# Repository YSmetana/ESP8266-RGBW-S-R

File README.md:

View this project on [CADLAB.io](https://cadlab.io/project/24310). 

# ESP8266-RGBW-S-R

**ESP8266**-based **RGBW** controller with **S**ensor and **R**elay support.

This harware design (PCB) is based on the [ESP-GO project and Hackitt & Bodgitt board](https://tech.scargill.net/home-control-2018/) created by [Pete Scargill](https://tech.scargill.net/) and [Aidan Ruff](https://www.scargill.net/cv/).

## PCB
96x55 mm.
### Render

### Actual photos
## Power supply
AC 110-220V or DC 5V, DC 5-24V.

### AC 110-220V, 5V needed
Use **PSU-A** HLK-PM01, output DC 5V. DC 3.3V via onboard LM1117-3.3.

### AC 110-220V, NO 5V needed
Use **PSU-D** HLK-2M03, output DC 3.3V. Short J4 to supply 3.3V directly from DC-DC convertor.

### DC 5V
Use **PSU-B** B0503S, output DC 3.3V. No onboard 3.3 regulator needed. Short J4 to supply 3.3V directly from DC-DC convertor.

### DC 5-24V
Use **PSU-C** LM2596-based buck convertor. Set output to 5V and use onboard LM1117-3.3. Or set output to 3.3V and short **J4** to supply 3.3V directly from DC-DC convertor.

## Errors found

In version **0.7** I was trying to use pull-down resistors for PWM output pins, but it turned out that ESP can not start if TX (GPIO1) pin is pulled low during the boot. So please just **remove R25** (don't solder it). PWM works fine without it (and probably without R22-R24 too :) ), and it was not in the original version.

I did not use R8 (remove) either because it seems it is duplicated by R11.

Apparently, GPIO4 and GPIO5 are misplaced on the schematic (correct on the PCB footprint).

## Soldering

### Basic

#### SMD
* LK2 - just short it if you use LED strip and use input power for them.
* R3
* R4
* R5
* R7
* R10
* R11
* R16
* R12
* C5
* C6
* ESP (sometimes better to solder manually to avoid shotage under the ESP)

If using non 3.3V input and need on-board linear converter:
* C2
* C3
* C4
* C22
* C27
* IC6

Short JP4 **only if you have 3.3V input** already and do not need any extra converters. Input 5V line will be directly connected with internal 3.3V line.

#### THT
* C1 (not nessecery with a good DC-DC converter with capacitor on-board)
* LED2 (status)
* X1 (for PWM RGBW) 
* JP10 (for programming)
* PSU (check voltage on regulated converters). See «Power supply» section above.

## Temp/Humidity sensor, IC2
### SMD
* R21

## PWM RGBW (3A/ch max)
### SMD
* R22
* R23
* R24
* R17
* R18
* R19
* R20
* Q3
* Q4
* Q5
* Q6

## Relay
Have not tested. Solder according to schematic.

## Programming
I did not use ATtiny85. To switch ESP to programming mode short pins **2** (PROG) and **6** (GND) on **JP3**.

## License

Shield: [![CC BY-SA 4.0][cc-by-sa-shield]][cc-by-sa]

This work is licensed under a
[Creative Commons Attribution-ShareAlike 4.0 International License][cc-by-sa].

[![CC BY-SA 4.0][cc-by-sa-image]][cc-by-sa]

[cc-by-sa]: http://creativecommons.org/licenses/by-sa/4.0/
[cc-by-sa-image]: https://licensebuttons.net/l/by-sa/4.0/88x31.png
[cc-by-sa-shield]: https://img.shields.io/badge/License-CC%20BY--SA%204.0-lightgrey.svg

## Disclaimer

THIS HARDWARE AND/OR SOFTWARE IS PROVIDED BY THE COPYRIGHT HOLDERS AND CONTRIBUTORS “AS IS” AND ANY EXPRESS OR IMPLIED WARRANTIES, INCLUDING, BUT NOT LIMITED TO, THE IMPLIED WARRANTIES OF MERCHANTABILITY AND FITNESS FOR A PARTICULAR PURPOSE ARE DISCLAIMED. IN NO EVENT SHALL THE COPYRIGHT OWNER OR CONTRIBUTORS BE LIABLE FOR ANY DIRECT, INDIRECT, INCIDENTAL, SPECIAL, EXEMPLARY, OR CONSEQUENTIAL DAMAGES (INCLUDING, BUT NOT LIMITED TO, PROCUREMENT OF SUBSTITUTE GOODS OR SERVICES; LOSS OF USE, DATA, OR PROFITS; OR BUSINESS INTERRUPTION) HOWEVER CAUSED AND ON ANY THEORY OF LIABILITY, WHETHER IN CONTRACT, STRICT LIABILITY, OR TORT (INCLUDING NEGLIGENCE OR OTHERWISE) ARISING IN ANY WAY OUT OF THE USE OF THIS SOFTWARE, EVEN IF ADVISED OF THE POSSIBILITY OF SUCH DAMAGE.

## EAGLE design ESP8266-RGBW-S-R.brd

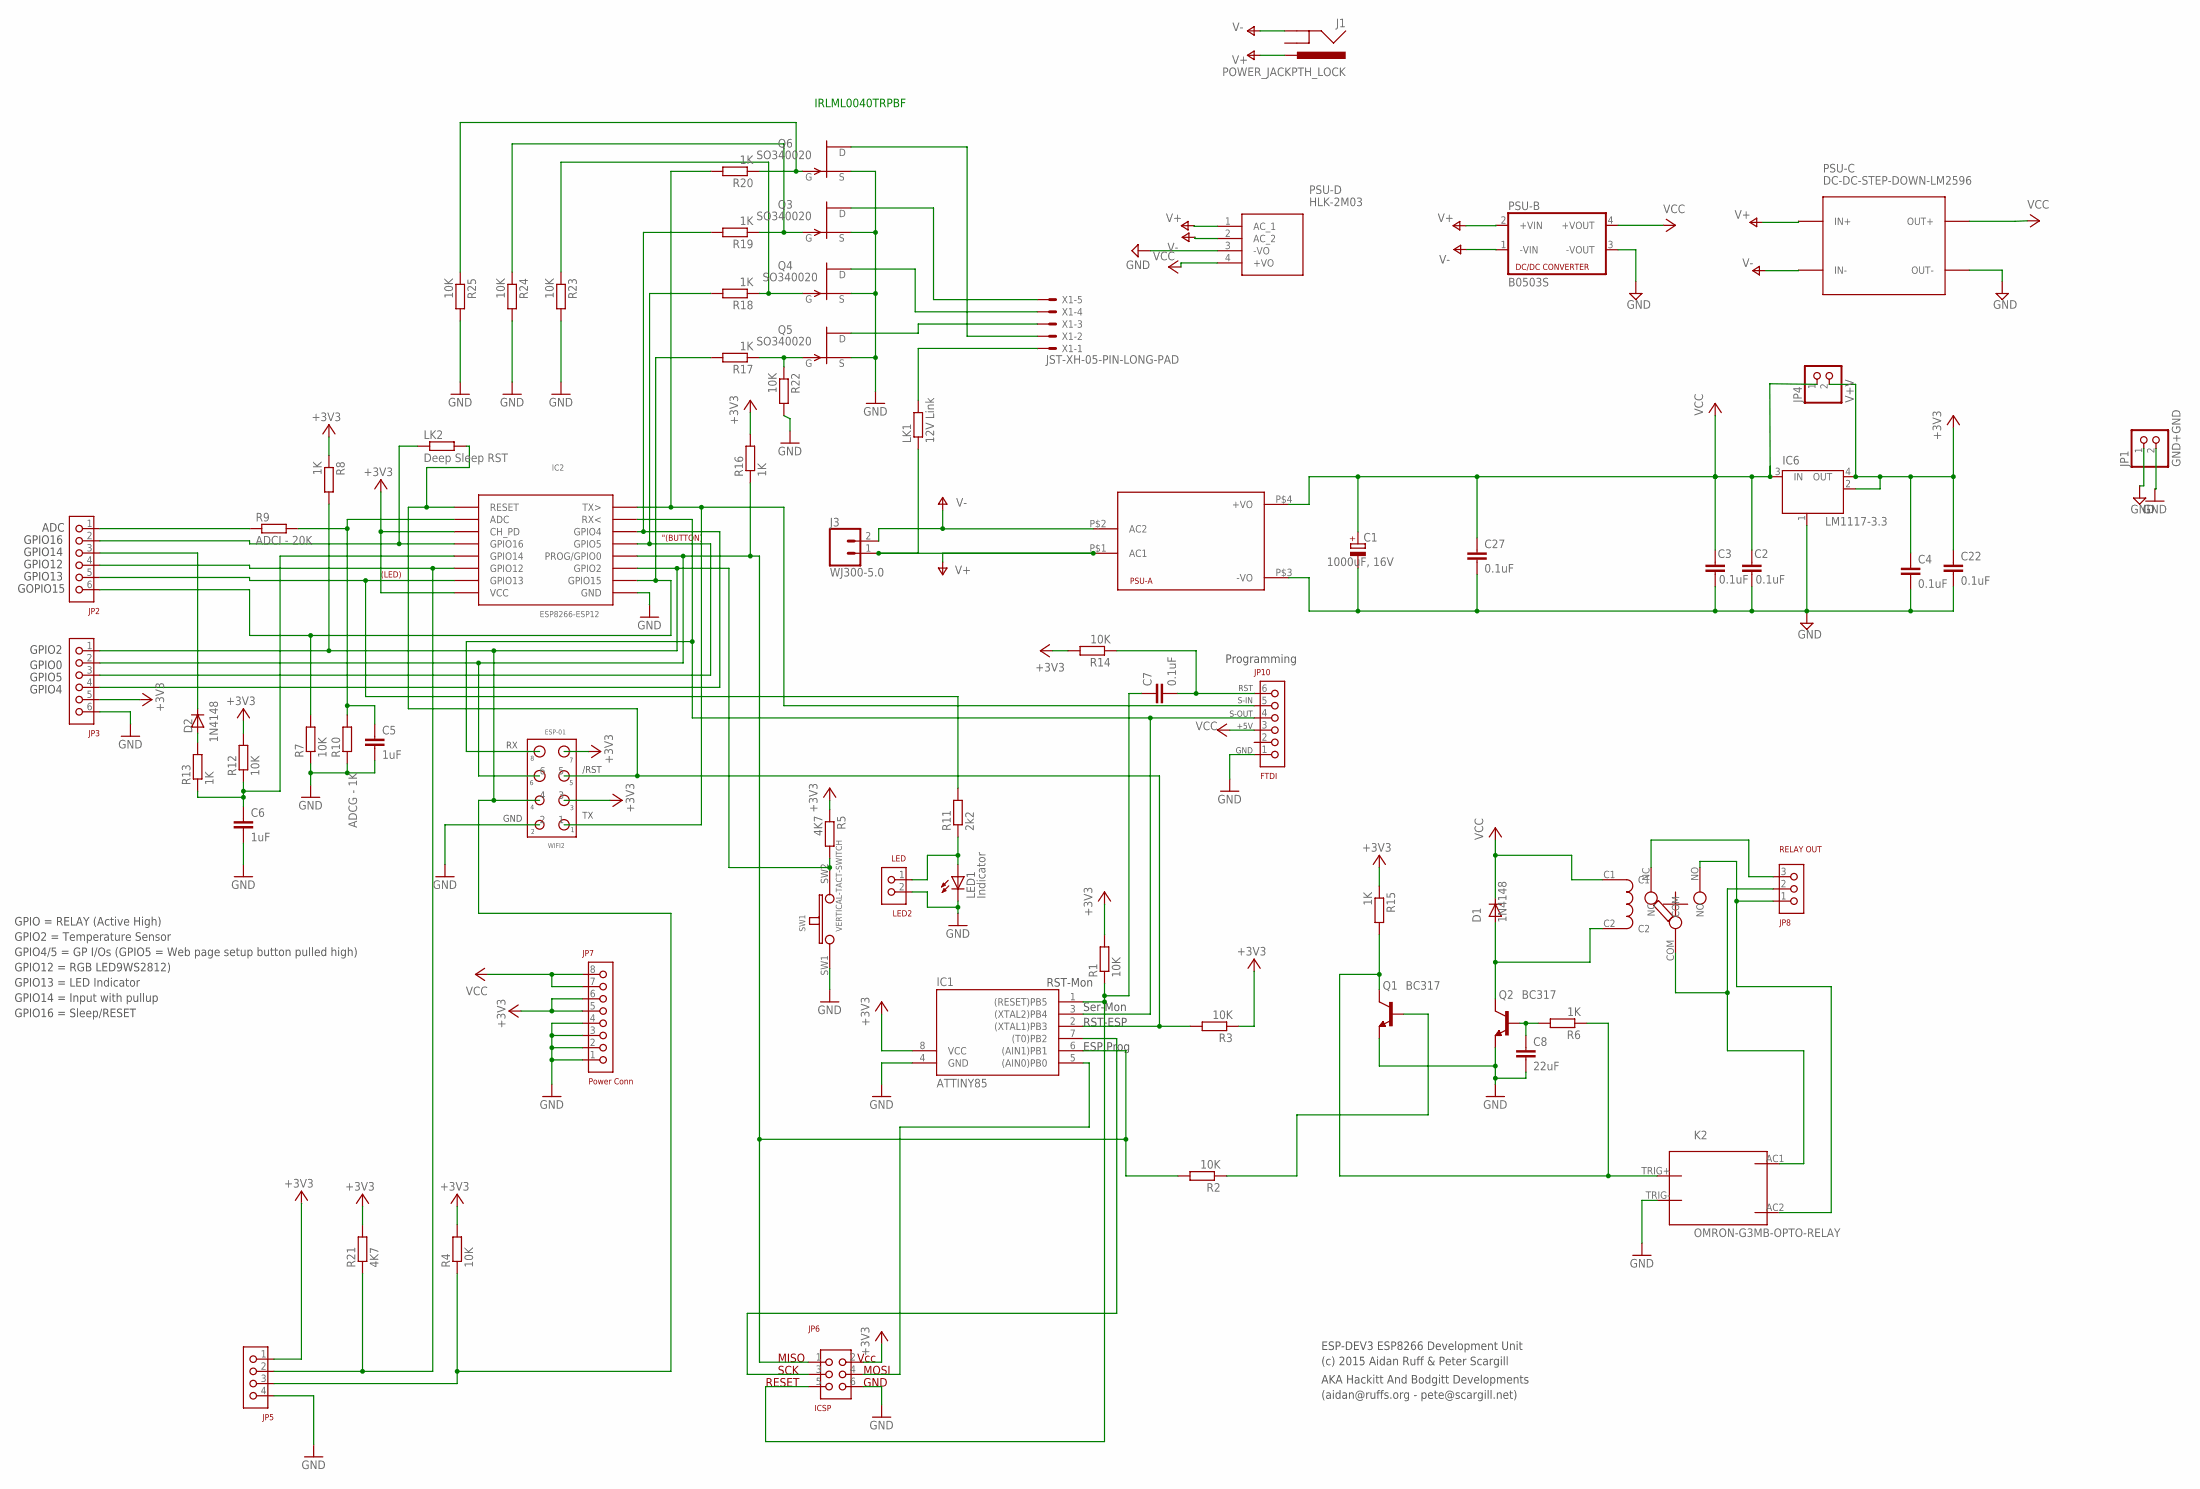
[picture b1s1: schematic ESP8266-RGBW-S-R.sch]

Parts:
C1: 1000uF, 16V; 150CLZ-1010
C2, C3, C4, C7, C22, C27: 0.1uF; C0805
C5, C6: 1uF; C0805
C8: 22uF; C0805
D1, D2: 1N4148; D0805
IC1: ATTINY85; SOIC8
IC2: ESP8266-ESP12; ESP8266-ESP12A
IC6: LM1117-3.3; SOT223
J1: POWER_JACKPTH_LOCK; POWER_JACK_PTH_LOCK
J3: WJ300-5.0; 1X02_XTRA_BIG
JP1: GND+GND; 1X02
JP2, JP3: HDR6X0.1
JP4: V+V; 1X02
JP5: HDR4X0.1
JP6: ICSP; HDR3X2X0.1
JP7: Power Conn; HDR8X0.1
JP8: RELAY OUT; 3X0.2
JP10: FTDI; HDR6X0.1
K1: SONGLE-RELAY-SPDT
K2: OMRON-G3MB-OPTO-RELAY
LED1: Indicator; CHIP-LED0805
LED2: LED; HDR2X0.1
LK1: 12V Link; R0805
LK2: Deep Sleep RST; R0805
PSU-A: HLK-PM013W; HLK-PM01
PSU-B: B0503S; NME
PSU-C: DC-DC-STEP-DOWN-LM2596
PSU-D: HLK-2M03; HLK2M03
Q1, Q2: BC317; SOT23-BEC
Q3, Q4, Q5, Q6: SO340020; SOT23
R1, R2, R3, R4, R7, R12, R14, R22, R23, R24, R25: 10K; R0805
R5, R21: 4K7; R0805
R6, R8, R13, R15, R16, R17, R18, R19, R20: 1K; R0805
R9: ADCI - 20K; R0805
R10: ADCG - 1K; R0805
R11: 2k2; R0805
SW1: VERTICAL-TACT-SWITCH
WIFI2: ESP-01; 4X2X0.1
X1: JST-XH-05-PIN-LONG-PAD; JST-XH-05-PACKAGE-LONG-PAD

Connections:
+3V3: C4.1, C22.1, IC1.8 (VCC), IC2.CH_PD, IC2.VCC, IC6.2 (OUT), IC6.4 (OUT), JP3.5, JP4.2, JP5.1, JP6.2, JP7.5, JP7.6, R1.2, R3.1, R4.2, R5.1, R8.1, R12.2, R14.2, R15.1, R16.2, R21.2, WIFI2.3, WIFI2.7
+VCC: C1.+, C2.1, C3.1, C27.1, D1.C, IC6.3 (IN), JP4.1, JP7.7, JP7.8, JP10.3, K1.C1, PSU-A.P$4 (+VO)
ADC: JP2.1, R9.1
GND: C1.-, C2.2, C3.2, C4.2, C5.2, C6.2, C8.2, C22.2, C27.2, IC1.4 (GND), IC2.GND, IC6.1 (GND/ADJ), JP1.1, JP1.2, JP3.6, JP5.4, JP6.6, JP7.1, JP7.2, JP7.3, JP7.4, JP10.1, K2.TRIG-, LED1.C, LED2.2, PSU-A.P$3 (-VO), PSU-B.3 (-VOUT), PSU-C.OUT-, PSU-D.3 (-VO), Q1.E, Q2.E, Q3.2 (S), Q4.2 (S), Q5.2 (S), Q6.2 (S), R7.1, R10.1, R22.2, R23.2, R24.2, R25.2, SW1.SW1, WIFI2.2
GPIO0: IC1.6 ((AIN1)PB1), IC2.PROG/GPIO0, JP3.2, JP6.1, R2.2, R16.1, WIFI2.6
GPIO2: IC2.GPIO2, JP3.1, JP5.3, R4.1, R5.2, R8.2, SW1.SW2, WIFI2.4
GPIO3: IC2.TXD (TX>), JP10.5, R20.2, WIFI2.1
GPIO4: IC2.GPIO4, JP3.4, R19.2
GPIO5: IC2.GPIO5, JP3.3, R18.2
GPIO13: IC2.GPIO13, JP2.5, R11.2
GPIO15: IC2.GPIO15, JP2.6, R7.2, R17.2
GPIO16: IC1.2 ((XTAL1)PB3), IC2.RESET, LK2.2, R3.2, WIFI2.5
MOSI: IC1.5 ((AIN0)PB0), JP6.4
unnamed: K2.TRIG+, Q1.C, R6.1, R15.2
unnamed: C5.1, IC2.ADC, R9.2, R10.2
unnamed: LED1.A, LED2.1, R11.1
unnamed: C6.1, IC2.GPIO14, R12.1, R13.1
unnamed: D2.A, R13.2
unnamed: IC1.3 ((XTAL2)PB4), IC2.RXD (RX<), JP10.4, WIFI2.8
unnamed: D2.C, JP2.3
unnamed: C7.2, JP10.6, R14.1
unnamed: IC2.GPIO12, JP2.4, JP5.2, R21.1
unnamed: Q6.3 (D), X1.2
unnamed: Q1.B, R2.1
unnamed: Q5.3 (D), X1.3
unnamed: JP8.2, K1.COM, K2.AC1
unnamed: JP8.1, K1.NO, K2.AC2
unnamed: JP8.3, K1.NC
unnamed: D1.A, K1.C2, Q2.C
unnamed: C8.1, Q2.B, R6.2
unnamed: Q4.3 (D), X1.4
unnamed: LK1.2, X1.1
unnamed: Q5.1 (G), R17.1, R22.1
unnamed: Q4.1 (G), R18.1, R23.1
unnamed: Q3.1 (G), R19.1, R24.1
unnamed: IC2.GPIO16, JP2.2, LK2.1
unnamed: Q3.3 (D), X1.5
unnamed: Q6.1 (G), R20.1, R25.1
RESET: C7.1, IC1.1 ((RESET)PB5), JP6.5, R1.1
SCLK: IC1.7 ((T0)PB2), JP6.3
V+: J1.PWR, J3.1, LK1.1, PSU-A.P$1 (AC1), PSU-B.2 (+VIN), PSU-C.IN+, PSU-D.1 (AC_1)
V-: J1.GND, J3.2, PSU-A.P$2 (AC2), PSU-B.1 (-VIN), PSU-C.IN-, PSU-D.2 (AC_2)
VCC: PSU-B.4 (+VOUT), PSU-C.OUT+, PSU-D.4 (+VO)

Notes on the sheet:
Programming
RST
S-IN
S-OUT
+5V
GND
/RST
RST-ESP
Ser-Mon
RST-Mon
ESP Prog
MISO
SCK
RESET
MOSI
Vcc
(LED)
"(BUTTON)
GPIO = RELAY (Active High)
GPIO2 = Temperature Sensor
GPIO4/5 = GP I/Os (GPIO5 = Web page setup button pulled high)
GPIO12 = RGB LED9WS2812)
GPIO13 = LED Indicator
GPIO14 = Input with pullup
GPIO16 = Sleep/RESET
ADC
GPIO16
GPIO14
GPIO12
GPIO13
GOPIO15
GPIO2
GPIO0
GPIO5
GPIO4
ESP-DEV3 ESP8266 Development Unit
AKA Hackitt And Bodgitt Developments
(c) 2015 Aidan Ruff & Peter Scargill
(aidan@ruffs.org - pete@scargill.net)
IRLML0040TRPBF

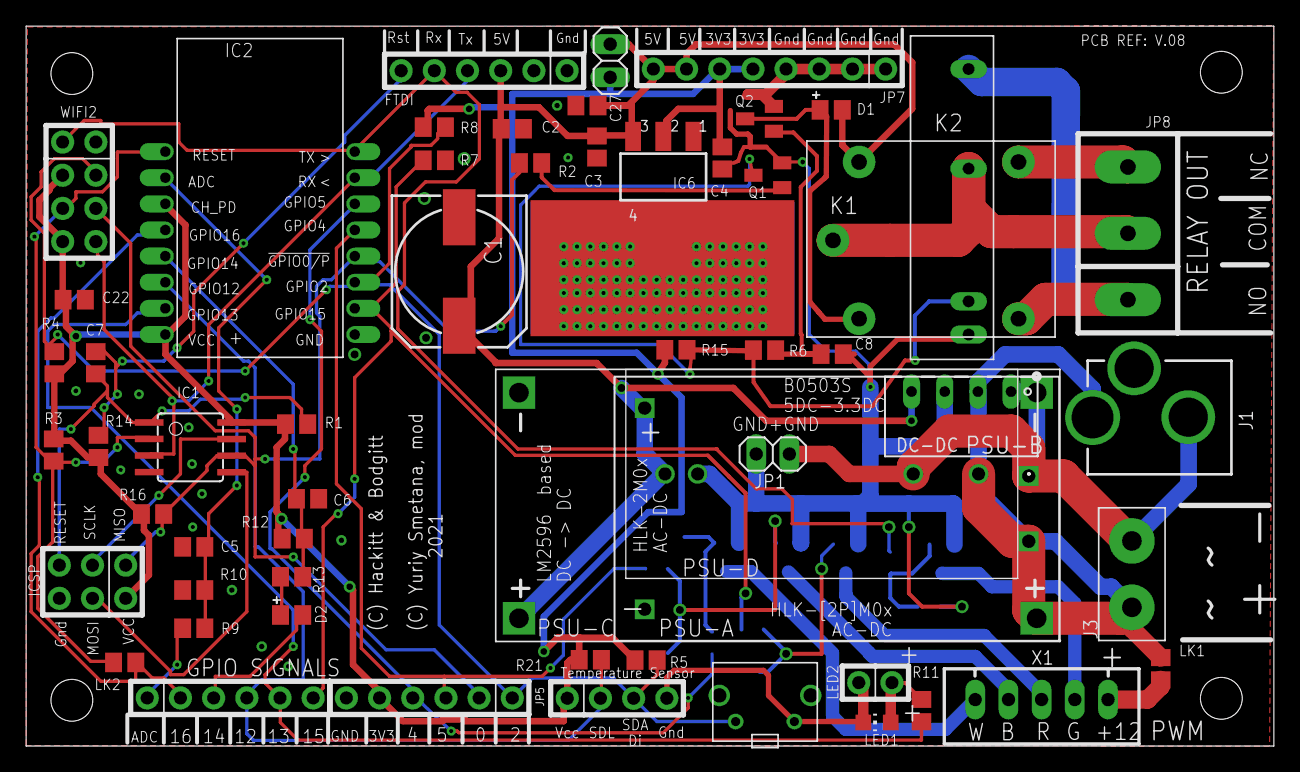
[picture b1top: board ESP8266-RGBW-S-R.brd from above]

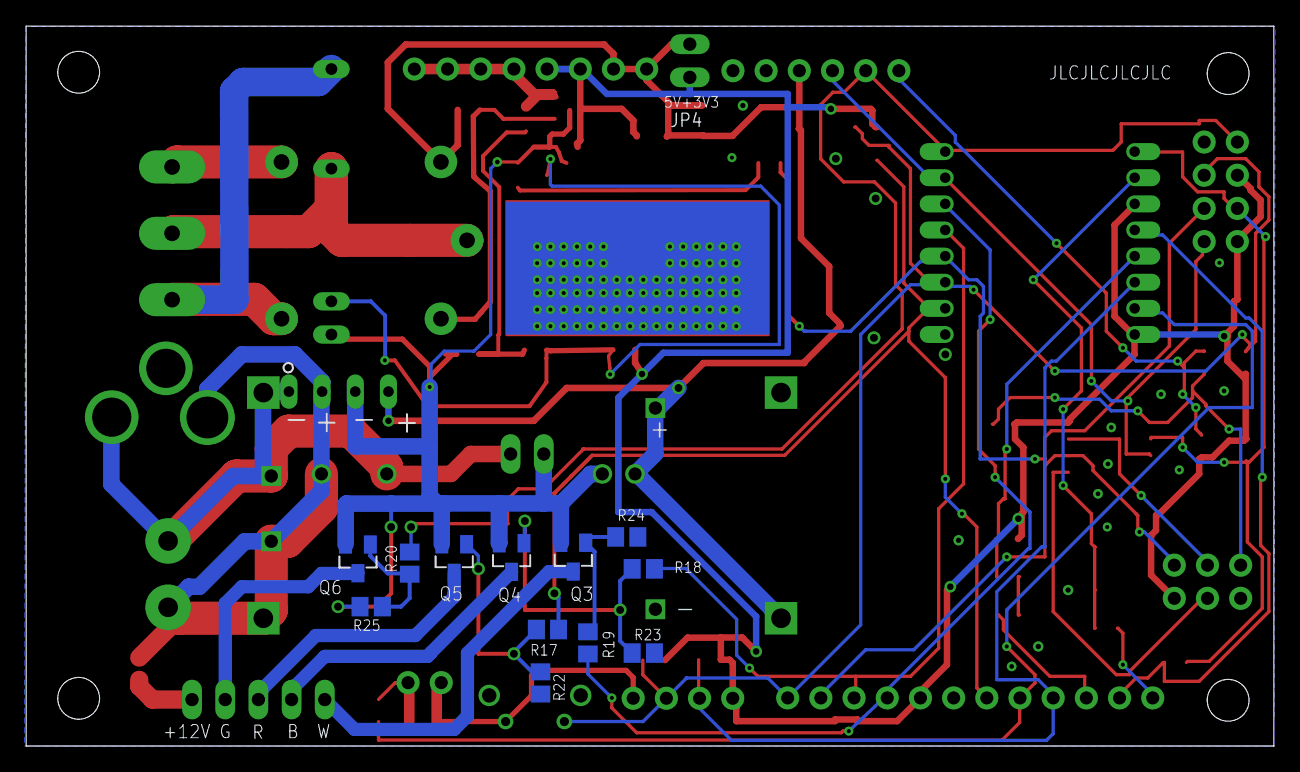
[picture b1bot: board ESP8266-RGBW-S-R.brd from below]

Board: 2 copper layers, 95.5 x 55.1 mm, 70 parts (12 on the bottom side), 43 nets.

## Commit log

2021-05-15 Backlink to CADLAB.io has been added.
2021-05-15 original schematic and PCB from ESP-GO project and Hackitt & Bodgitt board created by Pete Scargill and Aidan Ruff
2021-05-15 added White channel for PWM output
2021-05-15 alternative power subbly (DC-DC, AC-DC), alternative power jack as input
2021-05-15 v 0.6
2021-05-15 pull down resistors for the PWM control, some silkprint correction
2021-05-15 Gerber files
2021-05-15 render images
2021-05-15 r11 moved
2021-05-15 power supplies options
2021-05-17 readme edit
2021-05-17 images

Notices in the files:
parts and their libraries:
diy-modules: Released under the Creative Commons Attribution 4.0 International License: http://creativecommons.org/licenses/by/4.0
SparkFun-Connectors: Licensing: Creative Commons ShareAlike 4.0 International - https://creativecommons.org/licenses/by-sa/4.0
